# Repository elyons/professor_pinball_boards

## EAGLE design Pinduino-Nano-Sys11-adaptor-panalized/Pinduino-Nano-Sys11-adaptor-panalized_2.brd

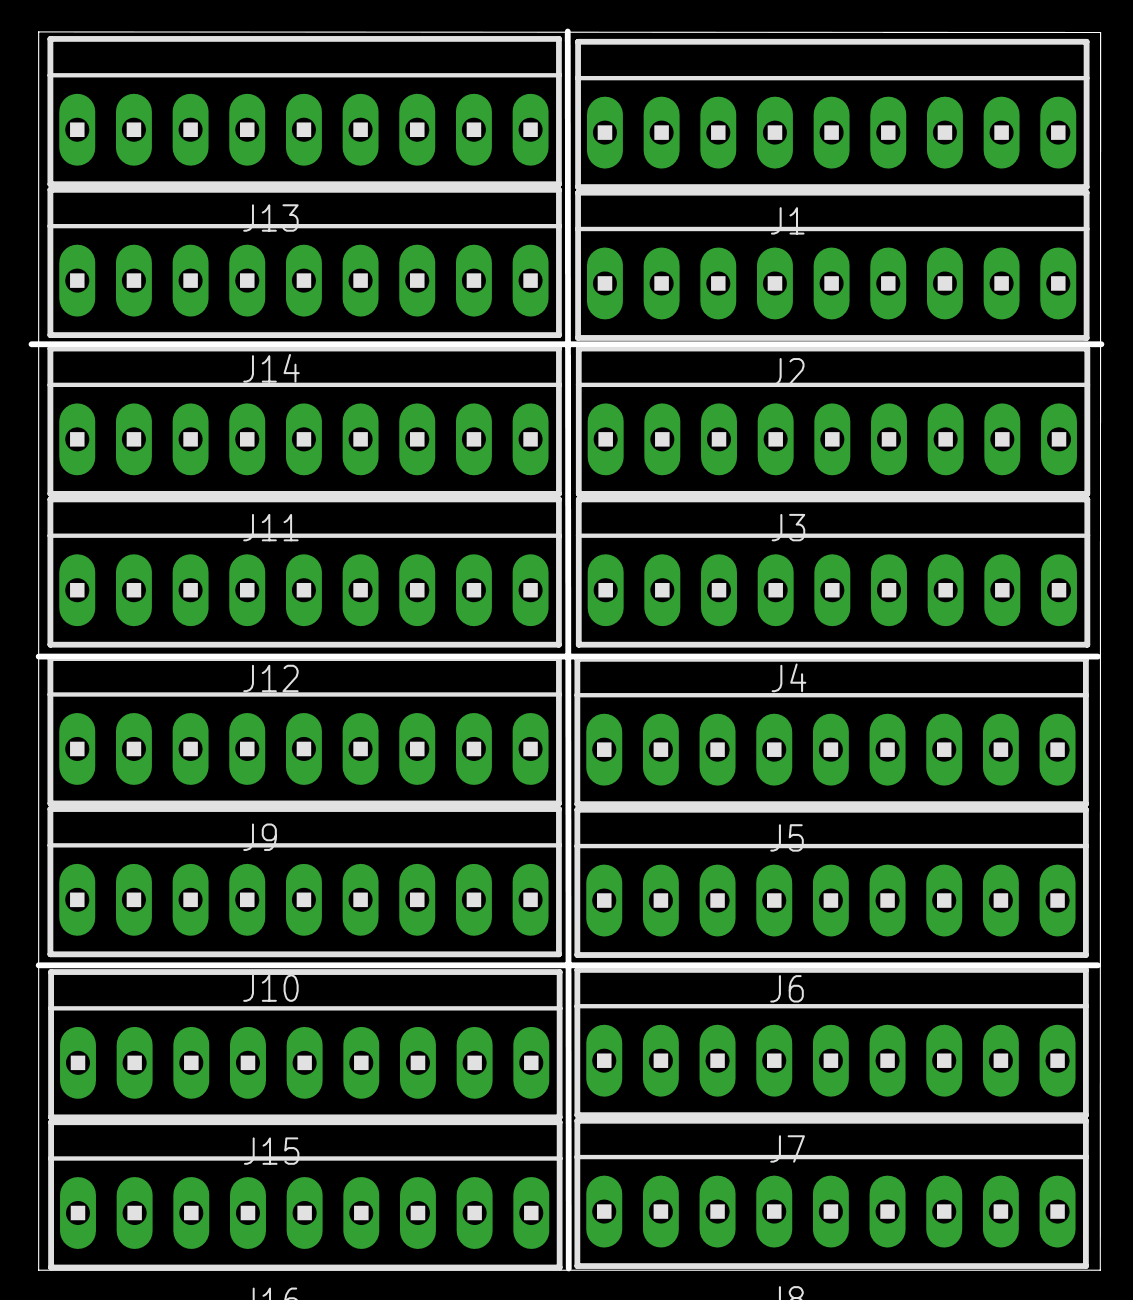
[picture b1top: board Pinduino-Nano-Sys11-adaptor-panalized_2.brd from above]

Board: 2 copper layers, 74.3 x 86.6 mm, 16 parts (0 on the bottom side), 72 nets, no tracks yet.

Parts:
J1, J2, J3, J4, J5, J6, J7, J8, J9, J10, J11, J12, J13, J14, J15, J16: 1X9MTA

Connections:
unnamed: J9.1, J10.1
unnamed: J9.2, J10.2
unnamed: J9.3, J10.3
unnamed: J9.4, J10.4
unnamed: J9.5, J10.5
unnamed: J9.7, J10.7
unnamed: J9.8, J10.8
unnamed: J9.9, J10.9
unnamed: J11.1, J12.1
unnamed: J11.2, J12.2
unnamed: J11.3, J12.3
unnamed: J11.4, J12.4
unnamed: J11.5, J12.5
unnamed: J11.7, J12.7
unnamed: J11.8, J12.8
unnamed: J11.9, J12.9
unnamed: J13.1, J14.1
unnamed: J13.2, J14.2
unnamed: J13.3, J14.3
unnamed: J13.4, J14.4
unnamed: J13.5, J14.5
unnamed: J13.7, J14.7
unnamed: J13.8, J14.8
unnamed: J13.9, J14.9
unnamed: J15.1, J16.1
unnamed: J15.2, J16.2
unnamed: J15.3, J16.3
unnamed: J15.4, J16.4
unnamed: J15.5, J16.5
unnamed: J15.7, J16.7
unnamed: J15.8, J16.8
unnamed: J15.9, J16.9
unnamed: J1.6, J2.6
unnamed: J1.1, J2.1
unnamed: J1.2, J2.2
unnamed: J1.3, J2.3
unnamed: J1.4, J2.4
unnamed: J1.5, J2.5
unnamed: J9.6, J10.6
unnamed: J1.7, J2.7
unnamed: J1.8, J2.8
unnamed: J1.9, J2.9
unnamed: J3.1, J4.1
unnamed: J3.2, J4.2
unnamed: J3.3, J4.3
unnamed: J3.4, J4.4
unnamed: J11.6, J12.6
unnamed: J13.6, J14.6
unnamed: J15.6, J16.6
unnamed: J3.5, J4.5
unnamed: J3.6, J4.6
unnamed: J3.7, J4.7
unnamed: J3.8, J4.8
unnamed: J3.9, J4.9
unnamed: J5.1, J6.1
unnamed: J5.2, J6.2
unnamed: J5.3, J6.3
unnamed: J5.4, J6.4
unnamed: J5.5, J6.5
unnamed: J5.6, J6.6
unnamed: J5.7, J6.7
unnamed: J5.8, J6.8
unnamed: J5.9, J6.9
unnamed: J7.1, J8.1
unnamed: J7.2, J8.2
unnamed: J7.3, J8.3
unnamed: J7.4, J8.4
unnamed: J7.5, J8.5
unnamed: J7.6, J8.6
unnamed: J7.7, J8.7
unnamed: J7.8, J8.8
unnamed: J7.9, J8.9

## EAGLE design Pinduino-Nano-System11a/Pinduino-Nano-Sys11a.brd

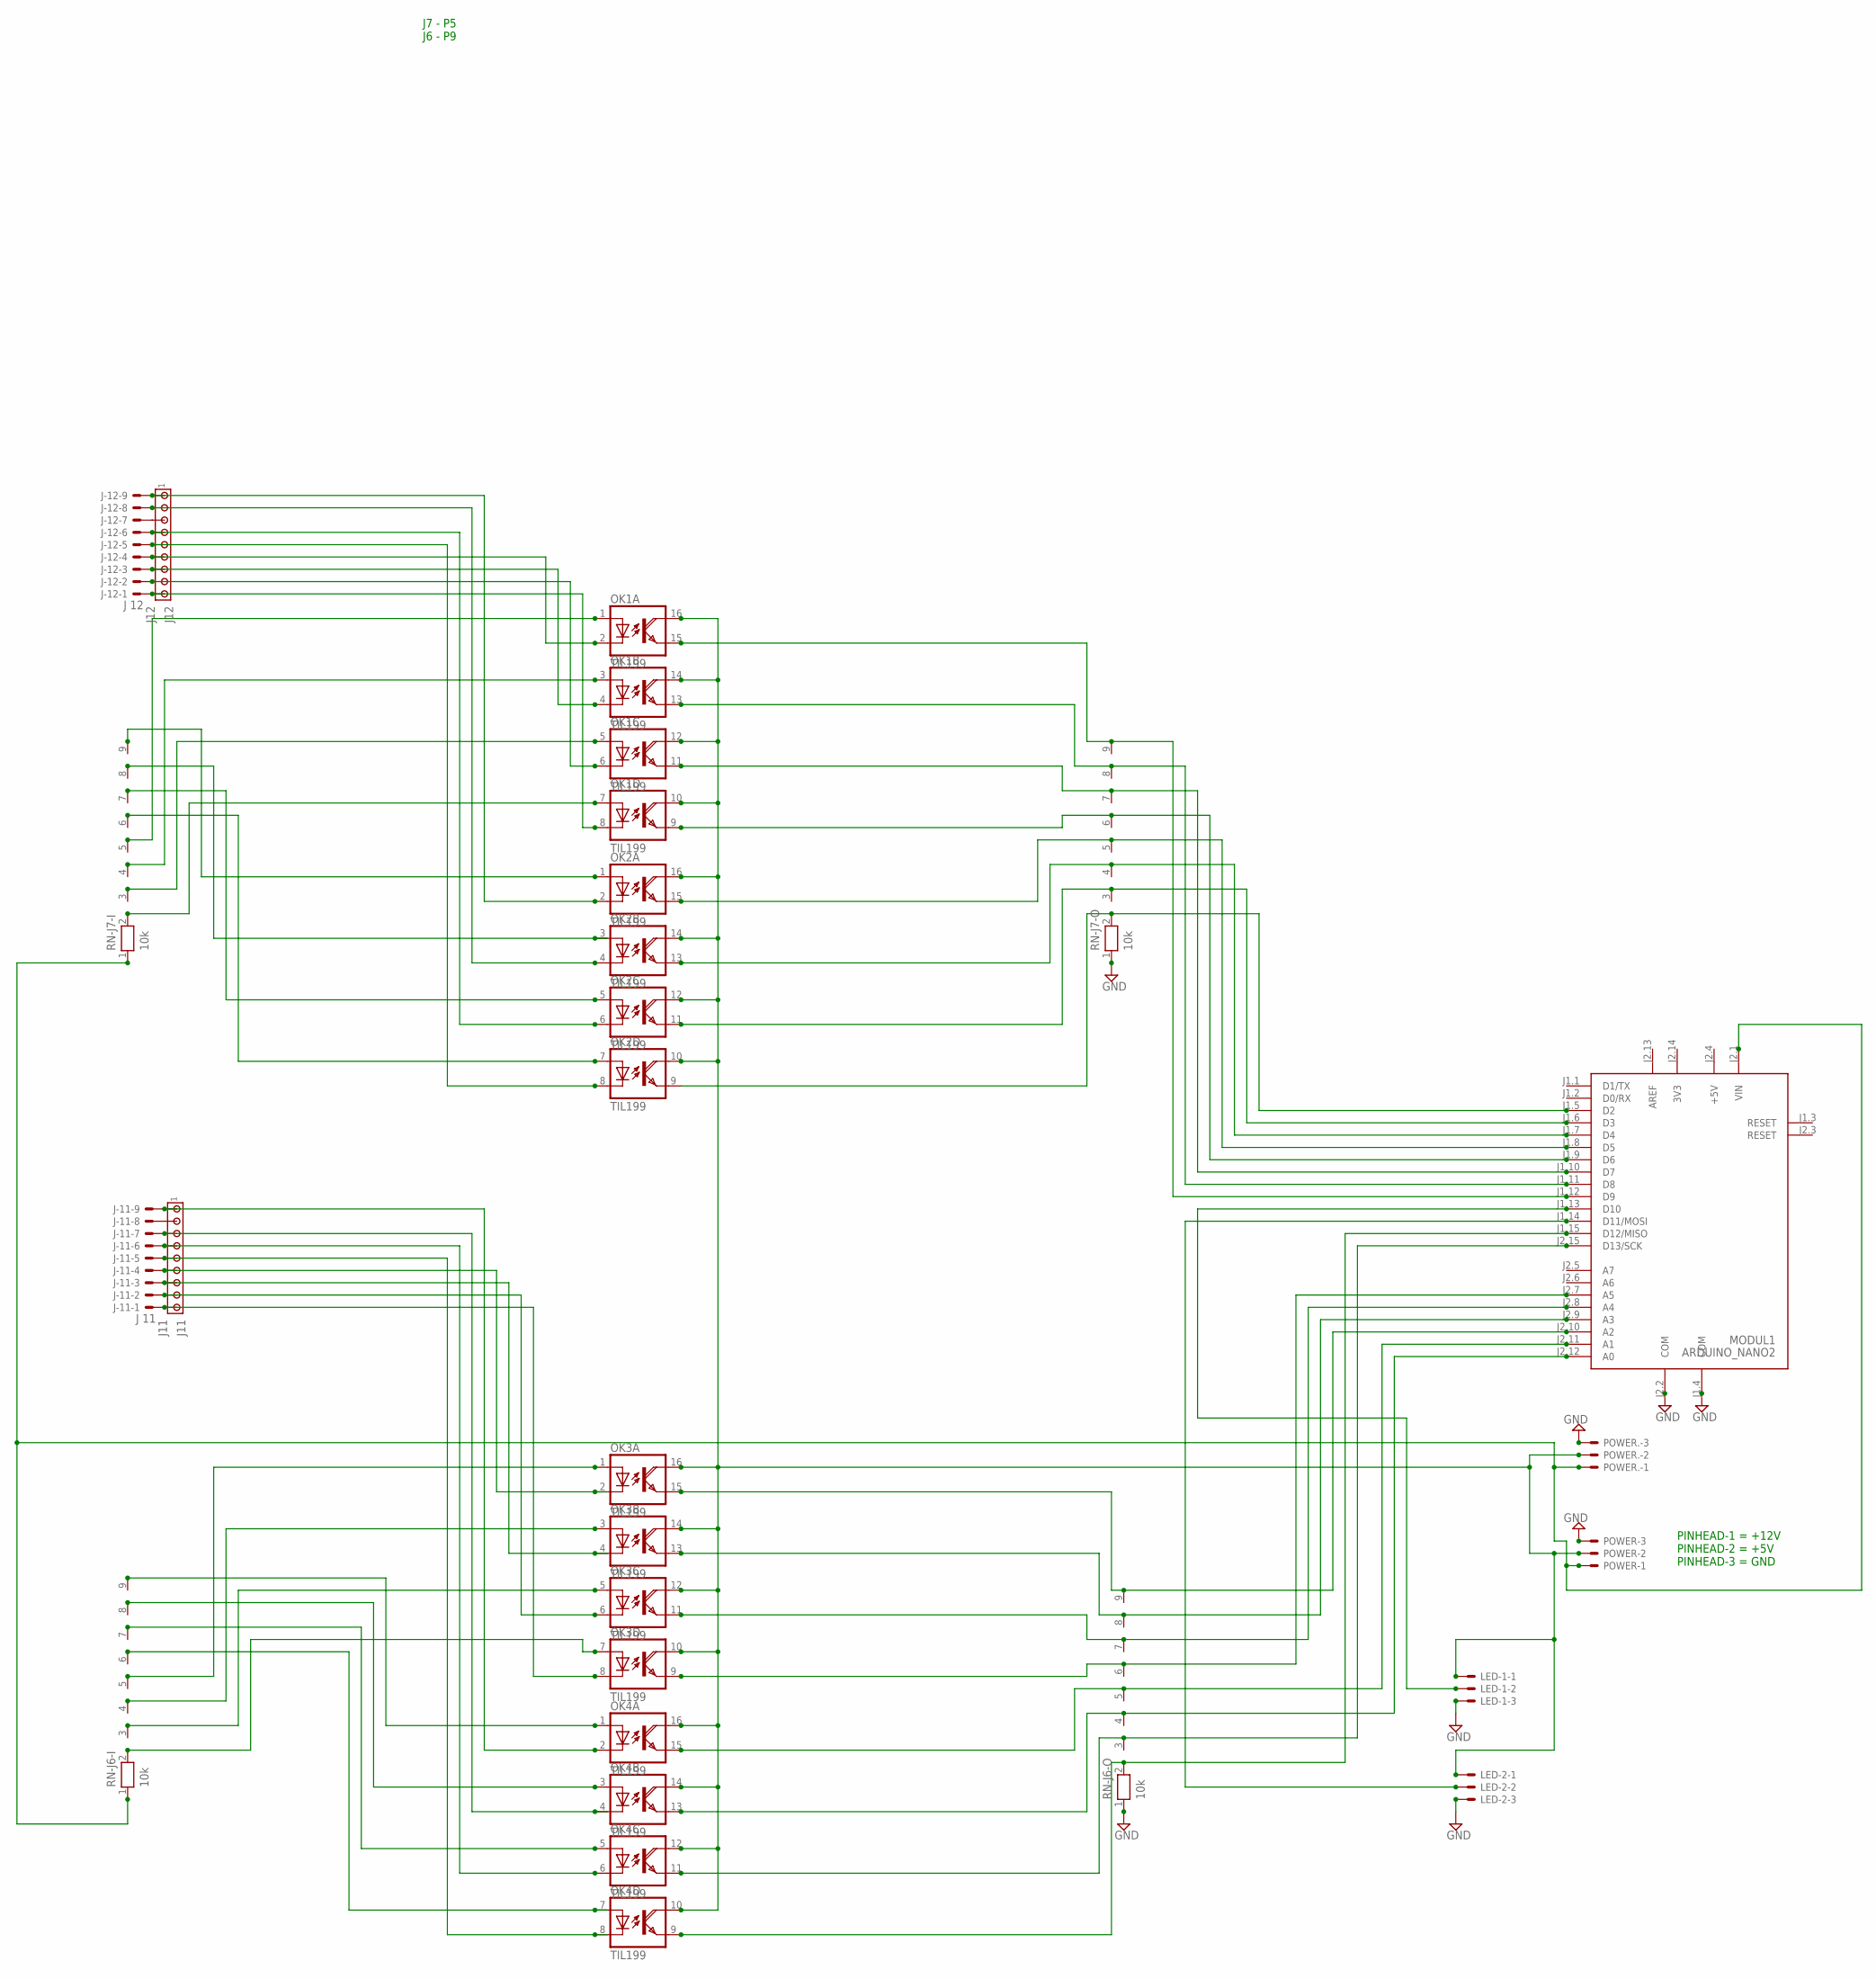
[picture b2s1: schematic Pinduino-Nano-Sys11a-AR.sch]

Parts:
J11: J11; 1X9MTA
J12: J12; 1X9MTA
J-11: J 11; KK-156-9
J-12: J 12; KK-156-9
LED-1, LED-2: 22-23-2031
MODUL1: ARDUINO_NANO2
OK1, OK2, OK3, OK4: TIL199; DIL16
POWER, POWER.: 22-23-2031
RN-J6-I, RN-J6-O, RN-J7-I, RN-J7-O: 10k; RN-9

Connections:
3V3: MODUL1.J2.14 (3V3)
+5V: MODUL1.J2.4 (+5V)
ARD+5V: LED-1.1, LED-2.1, OK1.10 (COL), OK1.12 (COL), OK1.14 (COL), OK1.16 (COL), OK2.10 (COL), OK2.12 (COL), OK2.14 (COL), OK2.16 (COL), OK3.10 (COL), OK3.12 (COL), OK3.14 (COL), OK3.16 (COL), OK4.10 (COL), OK4.12 (COL), OK4.14 (COL), OK4.16 (COL), POWER.2, POWER..2
AREF: MODUL1.J2.13 (AREF)
GND: LED-1.3, LED-2.3, MODUL1.J1.4 (COM), MODUL1.J2.2 (COM), POWER.3, POWER..3, RN-J6-O.1, RN-J7-O.1
unnamed: J12.6, J-12.4, OK1.2 (C)
unnamed: MODUL1.J1.5 (D2), OK2.9 (EMI), RN-J7-O.2
unnamed: OK1.3 (A), RN-J7-I.4
unnamed: OK1.5 (A), RN-J7-I.3
unnamed: OK1.7 (A), RN-J7-I.2
unnamed: OK2.1 (A), RN-J7-I.9
unnamed: OK2.3 (A), RN-J7-I.8
unnamed: OK2.5 (A), RN-J7-I.7
unnamed: OK1.1 (A), RN-J7-I.5
unnamed: J12.9, J-12.1, OK1.8 (C)
unnamed: J12.8, J-12.2, OK1.6 (C)
unnamed: J12.7, J-12.3, OK1.4 (C)
unnamed: OK2.7 (A), RN-J7-I.6
unnamed: J12.5, J-12.5, OK2.8 (C)
unnamed: J11.9, J-11.1, OK3.8 (C)
unnamed: J12.2, J-12.8, OK2.4 (C)
unnamed: J12.1, J-12.9, OK2.2 (C)
unnamed: MODUL1.J1.6 (D3), OK2.11 (EMI), RN-J7-O.3
unnamed: J11.7, J-11.3, OK3.4 (C)
unnamed: J11.5, J-11.5, OK4.8 (C)
unnamed: J11.4, J-11.6, OK4.6 (C)
unnamed: J11.3, J-11.7, OK4.4 (C)
unnamed: J12.3, J-12.7
unnamed: MODUL1.J1.11 (D8), OK1.13 (EMI), RN-J7-O.8
unnamed: J11.2, J-11.8
unnamed: J11.1, J-11.9, OK4.2 (C)
unnamed: MODUL1.J1.7 (D4), OK2.13 (EMI), RN-J7-O.4
unnamed: OK4.1 (A), RN-J6-I.9
unnamed: OK4.3 (A), RN-J6-I.8
unnamed: OK4.5 (A), RN-J6-I.7
unnamed: OK3.3 (A), RN-J6-I.4
unnamed: OK3.1 (A), RN-J6-I.5
unnamed: OK3.5 (A), RN-J6-I.3
unnamed: OK4.7 (A), RN-J6-I.6
unnamed: MODUL1.J2.8 (A4), OK3.11 (EMI), RN-J6-O.7
unnamed: OK3.7 (A), RN-J6-I.2
unnamed: MODUL1.J2.7 (A5), OK3.9 (EMI), RN-J6-O.6
unnamed: MODUL1.J2.15 (D13/SCK), OK4.11 (EMI), RN-J6-O.3
unnamed: J11.8, J-11.2, OK3.6 (C)
unnamed: MODUL1.J2.12 (A0), OK4.13 (EMI), RN-J6-O.4
unnamed: MODUL1.J2.11 (A1), OK4.15 (EMI), RN-J6-O.5
unnamed: LED-2.2, MODUL1.J1.14 (D11/MOSI)
unnamed: LED-1.2, MODUL1.J1.13 (D10)
unnamed: MODUL1.J1.12 (D9), OK1.15 (EMI), RN-J7-O.9
unnamed: J12.4, J-12.6, OK2.6 (C)
unnamed: J11.6, J-11.4, OK3.2 (C)
unnamed: MODUL1.J1.10 (D7), OK1.11 (EMI), RN-J7-O.7
unnamed: MODUL1.J1.8 (D5), OK2.15 (EMI), RN-J7-O.5
unnamed: MODUL1.J1.9 (D6), OK1.9 (EMI), RN-J7-O.6
unnamed: MODUL1.J2.9 (A3), OK3.13 (EMI), RN-J6-O.8
unnamed: MODUL1.J2.10 (A2), OK3.15 (EMI), RN-J6-O.9
unnamed: MODUL1.J1.15 (D12/MISO), OK4.9 (EMI), RN-J6-O.2
unnamed: MODUL1.J2.1 (VIN), POWER.1, POWER..1, RN-J6-I.1, RN-J7-I.1

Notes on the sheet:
J7 - P5 J6 - P9
PINHEAD-1 = +12V PINHEAD-2 = +5V PINHEAD-3 = GND

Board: 2 copper layers, 17 parts (0 on the bottom side), 55 nets, no tracks yet.

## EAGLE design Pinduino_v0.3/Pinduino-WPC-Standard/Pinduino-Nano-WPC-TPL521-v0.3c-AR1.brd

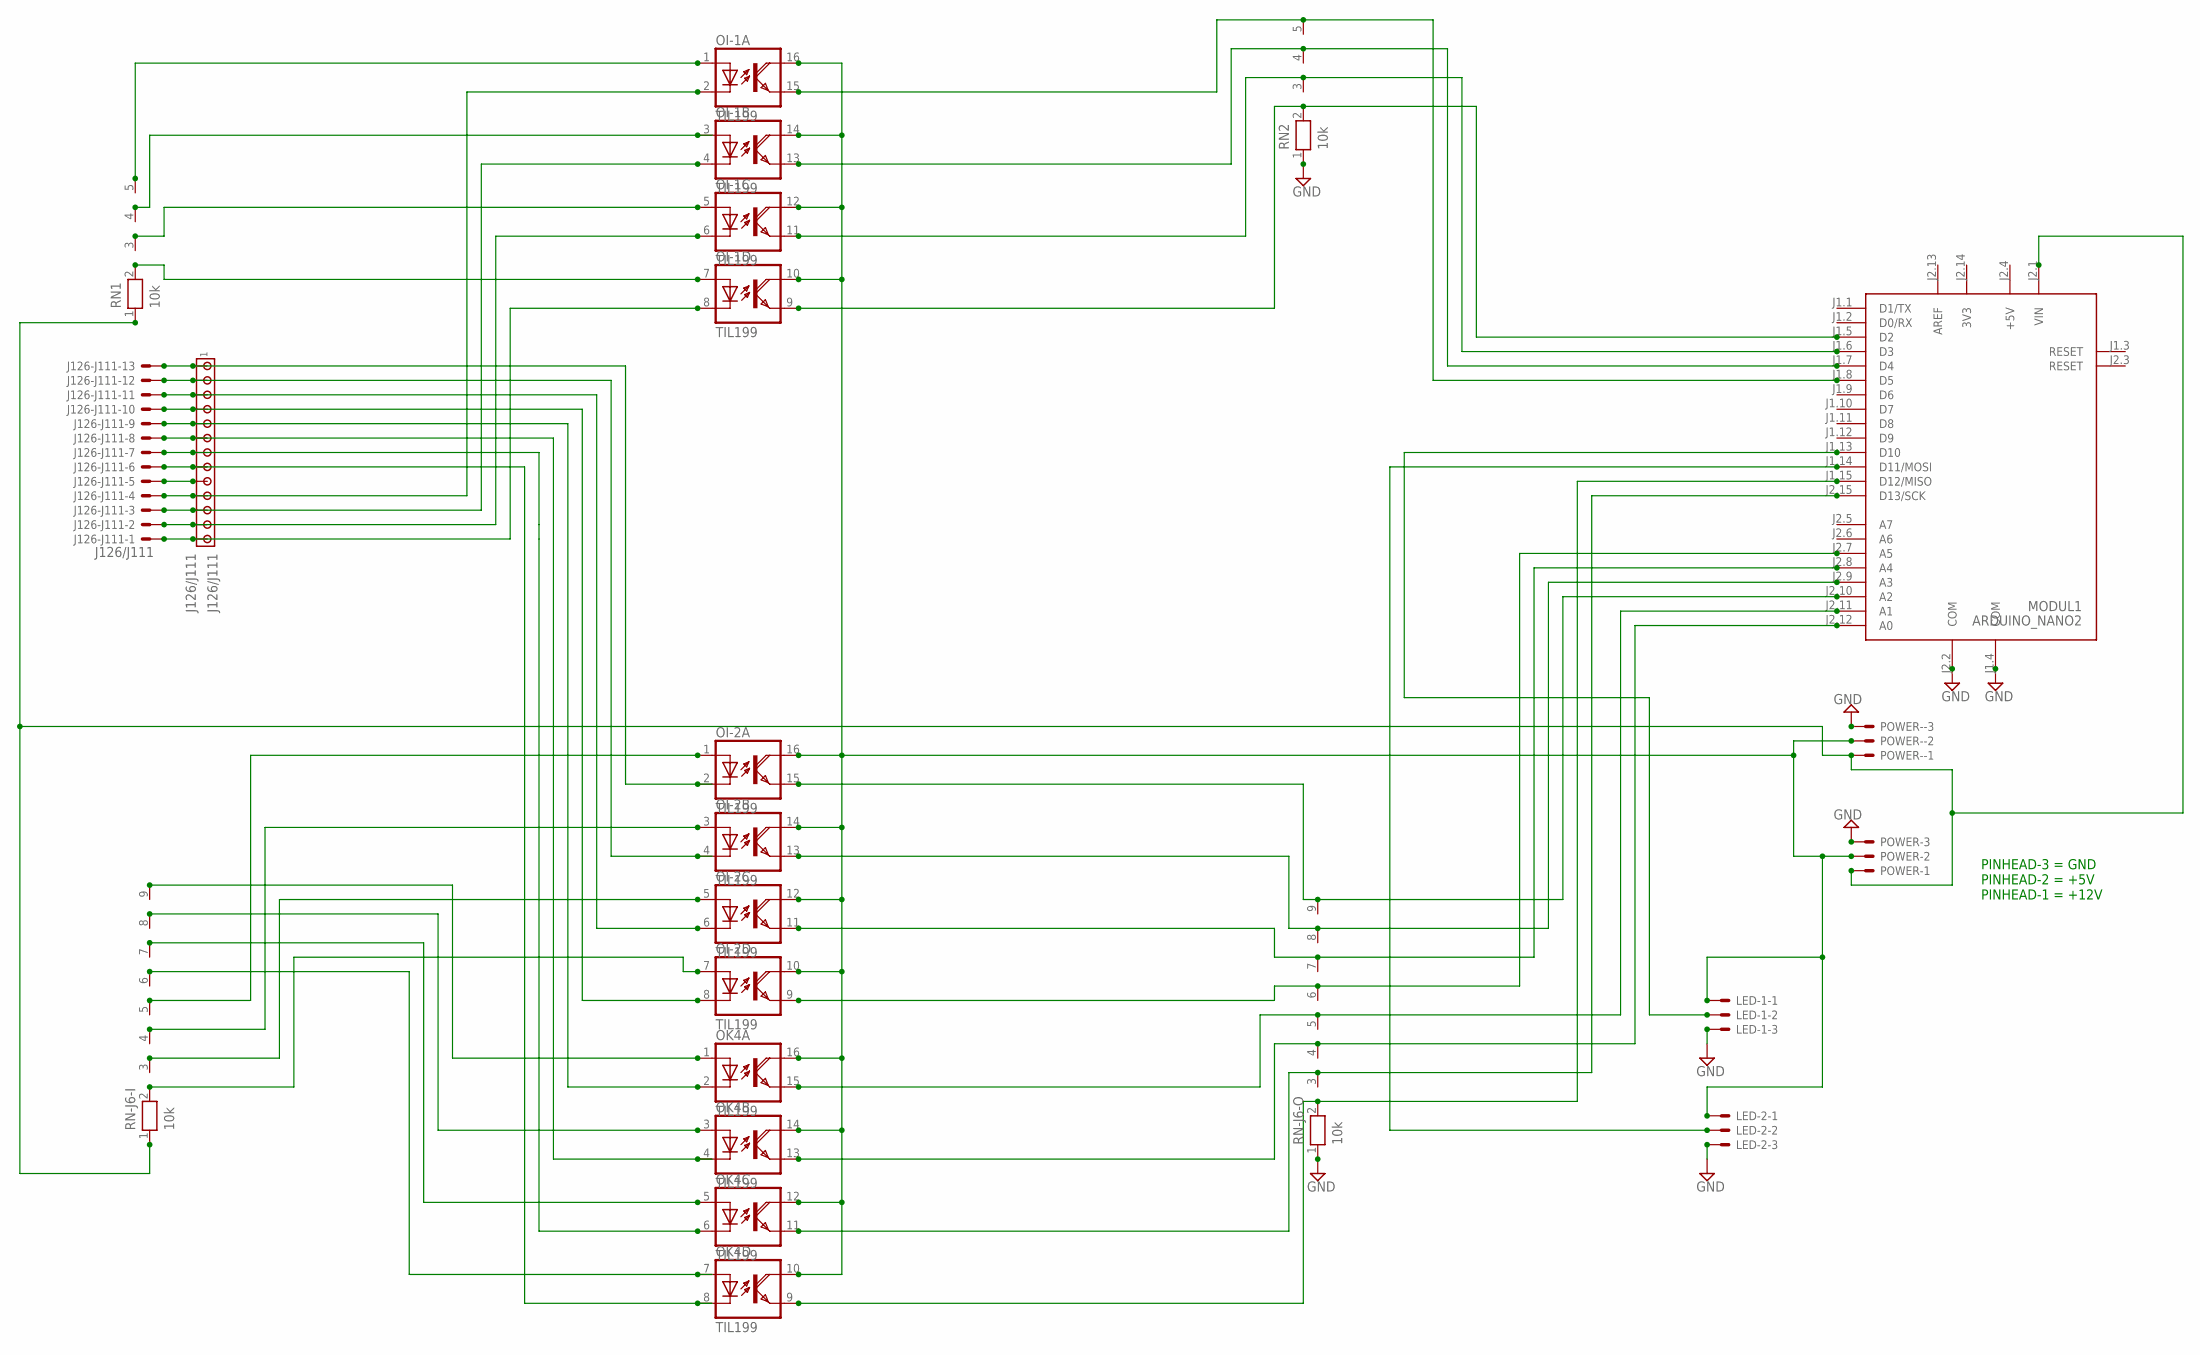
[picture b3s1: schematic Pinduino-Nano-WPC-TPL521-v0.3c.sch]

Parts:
J126-J111: J126/J111; KK-156-13
J126/J111: J126/J111; 1X13MTA
LED-1, LED-2: 22-23-2031
MODUL1: ARDUINO_NANO2
OI-1, OI-2: TIL199; DIL16
OK4: TIL199; DIL16
POWER: 22-23-2031
POWER-: 22-23-2031
RN1, RN2: 10k; RN-5
RN-J6-I, RN-J6-O: 10k; RN-9

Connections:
3V3: MODUL1.J2.14 (3V3)
+5V: MODUL1.J2.4 (+5V)
ARD+5V: LED-1.1, LED-2.1, OI-1.10 (COL), OI-1.12 (COL), OI-1.14 (COL), OI-1.16 (COL), OI-2.10 (COL), OI-2.12 (COL), OI-2.14 (COL), OI-2.16 (COL), OK4.10 (COL), OK4.12 (COL), OK4.14 (COL), OK4.16 (COL), POWER.2, POWER-.2
AREF: MODUL1.J2.13 (AREF)
GND: LED-1.3, LED-2.3, MODUL1.J1.4 (COM), MODUL1.J2.2 (COM), POWER.3, POWER-.3, RN2.1, RN-J6-O.1
unnamed: MODUL1.J2.1 (VIN), POWER.1, POWER-.1, RN1.1, RN-J6-I.1
unnamed: MODUL1.J1.5 (D2), OI-1.9 (EMI), RN2.2
unnamed: OI-1.5 (A), RN1.3
unnamed: OI-1.1 (A), RN1.5
unnamed: OI-1.3 (A), RN1.4
unnamed: OI-1.7 (A), RN1.2
unnamed: MODUL1.J1.6 (D3), OI-1.11 (EMI), RN2.3
unnamed: J126-J111.3, J126/J111.11, OI-1.4 (C)
unnamed: J126-J111.2, J126/J111.12, OI-1.6 (C)
unnamed: J126-J111.12, J126/J111.2, OI-2.4 (C)
unnamed: J126-J111.13, J126/J111.1, OI-2.2 (C)
unnamed: J126-J111.4, J126/J111.10, OI-1.2 (C)
unnamed: J126-J111.1, J126/J111.13, OI-1.8 (C)
unnamed: J126-J111.9, J126/J111.5, OK4.2 (C)
unnamed: MODUL1.J1.7 (D4), OI-1.13 (EMI), RN2.4
unnamed: OK4.1 (A), RN-J6-I.9
unnamed: OK4.3 (A), RN-J6-I.8
unnamed: OK4.5 (A), RN-J6-I.7
unnamed: OI-2.3 (A), RN-J6-I.4
unnamed: OI-2.1 (A), RN-J6-I.5
unnamed: OI-2.5 (A), RN-J6-I.3
unnamed: OK4.7 (A), RN-J6-I.6
unnamed: MODUL1.J2.8 (A4), OI-2.11 (EMI), RN-J6-O.7
unnamed: OI-2.7 (A), RN-J6-I.2
unnamed: MODUL1.J2.7 (A5), OI-2.9 (EMI), RN-J6-O.6
unnamed: MODUL1.J2.15 (D13/SCK), OK4.11 (EMI), RN-J6-O.3
unnamed: MODUL1.J2.12 (A0), OK4.13 (EMI), RN-J6-O.4
unnamed: MODUL1.J2.11 (A1), OK4.15 (EMI), RN-J6-O.5
unnamed: LED-2.2, MODUL1.J1.14 (D11/MOSI)
unnamed: LED-1.2, MODUL1.J1.13 (D10)
unnamed: MODUL1.J1.8 (D5), OI-1.15 (EMI), RN2.5
unnamed: MODUL1.J2.9 (A3), OI-2.13 (EMI), RN-J6-O.8
unnamed: MODUL1.J2.10 (A2), OI-2.15 (EMI), RN-J6-O.9
unnamed: J126-J111.6, J126/J111.8, OK4.8 (C)
unnamed: J126-J111.7, J126/J111.7, OK4.6 (C)
unnamed: MODUL1.J1.15 (D12/MISO), OK4.9 (EMI), RN-J6-O.2
unnamed: J126-J111.8, J126/J111.6, OK4.4 (C)
unnamed: J126-J111.5, J126/J111.9
unnamed: J126-J111.10, J126/J111.4, OI-2.8 (C)
unnamed: J126-J111.11, J126/J111.3, OI-2.6 (C)

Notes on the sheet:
PINHEAD-3 = GND PINHEAD-2 = +5V PINHEAD-1 = +12V

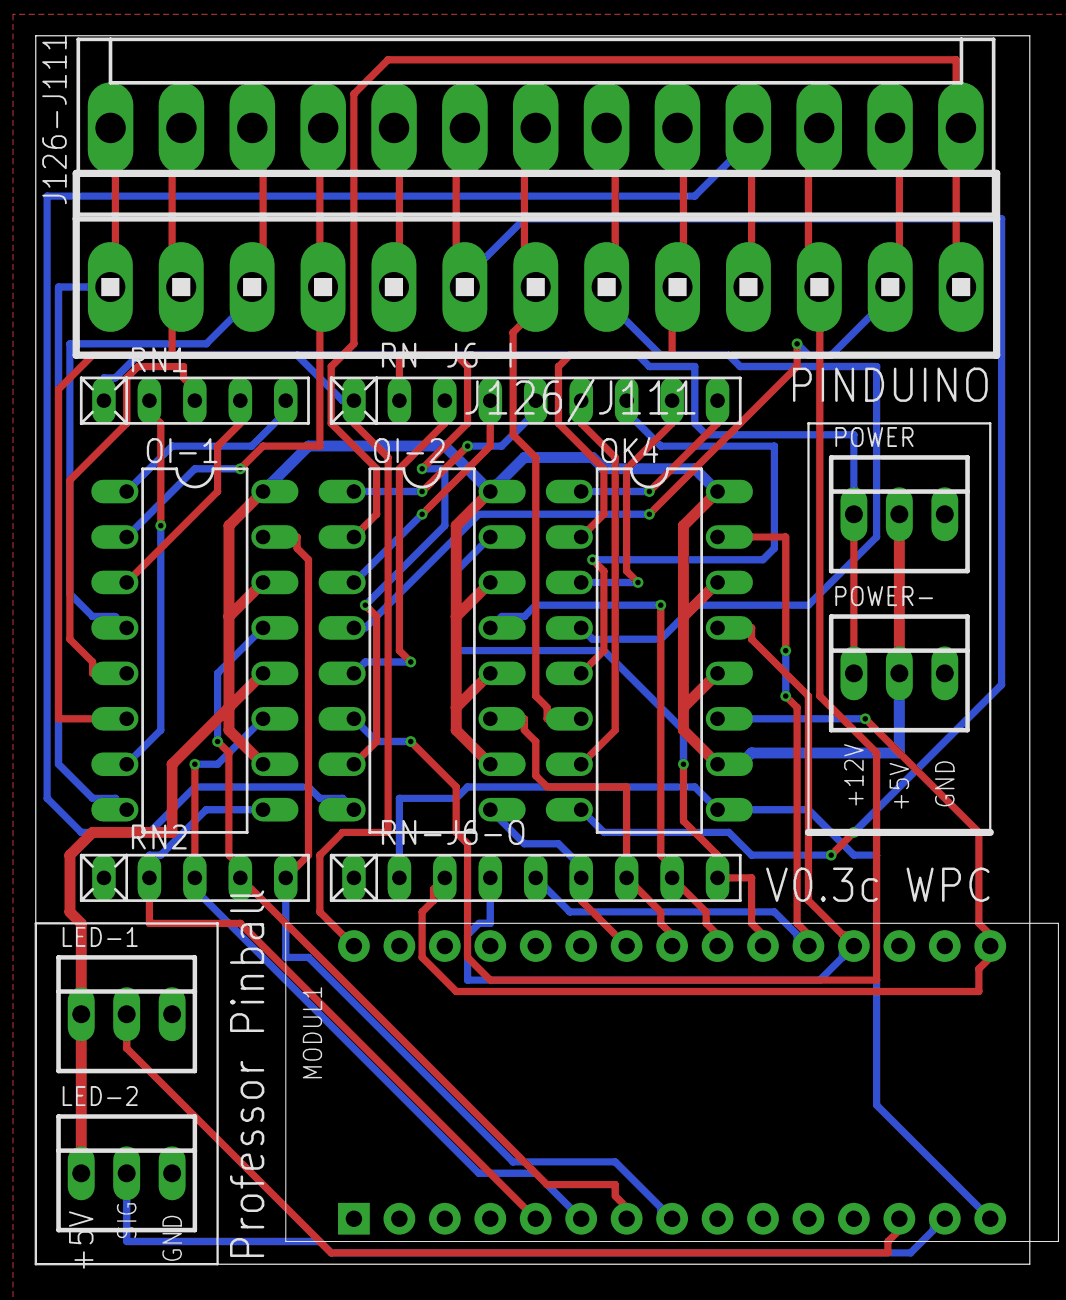
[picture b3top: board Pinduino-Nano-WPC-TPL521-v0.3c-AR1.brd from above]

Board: 2 copper layers, 55.6 x 68.7 mm, 14 parts (0 on the bottom side), 42 nets.

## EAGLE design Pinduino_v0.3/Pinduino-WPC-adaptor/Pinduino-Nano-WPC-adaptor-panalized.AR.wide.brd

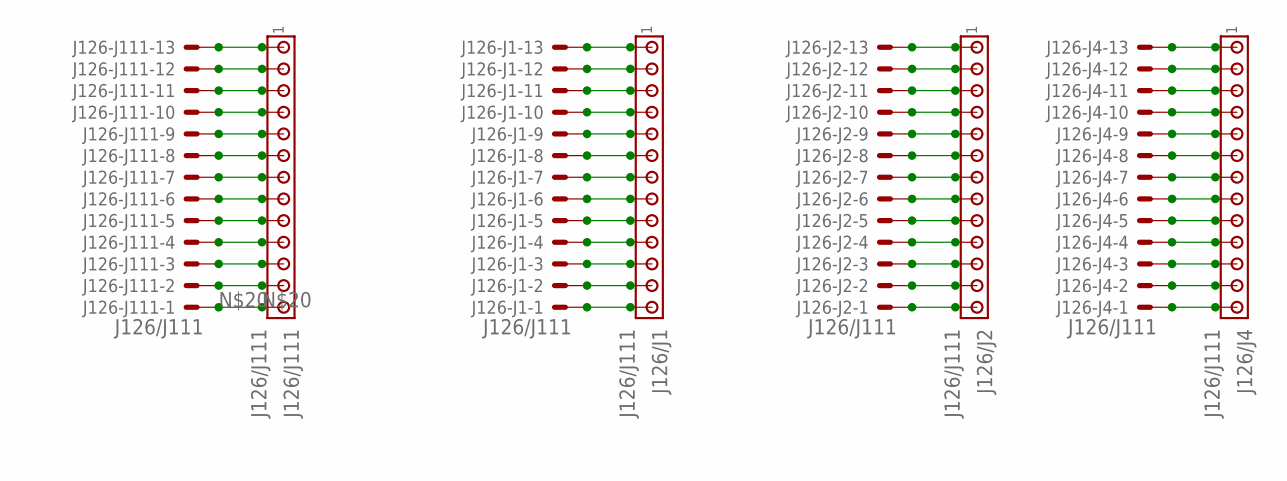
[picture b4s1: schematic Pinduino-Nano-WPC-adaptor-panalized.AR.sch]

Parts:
J126-J1, J126-J2, J126-J4, J126-J111: J126/J111; KK-156-13
J126/J1, J126/J2, J126/J4, J126/J111: J126/J111; 1X13MTA

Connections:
unnamed: J126-J1.12, J126/J1.2
unnamed: J126-J1.13, J126/J1.1
unnamed: J126-J1.9, J126/J1.5
unnamed: J126-J1.5, J126/J1.9
unnamed: J126-J1.6, J126/J1.8
unnamed: J126-J1.7, J126/J1.7
unnamed: J126-J1.8, J126/J1.6
unnamed: J126-J1.10, J126/J1.4
unnamed: J126-J1.11, J126/J1.3
unnamed: J126-J1.4, J126/J1.10
unnamed: J126-J1.3, J126/J1.11
unnamed: J126-J1.2, J126/J1.12
unnamed: J126-J1.1, J126/J1.13
unnamed: J126-J2.12, J126/J2.2
unnamed: J126-J2.13, J126/J2.1
unnamed: J126-J2.9, J126/J2.5
unnamed: J126-J2.5, J126/J2.9
unnamed: J126-J2.6, J126/J2.8
unnamed: J126-J111.3, J126/J111.11
unnamed: J126-J111.2, J126/J111.12
unnamed: J126-J111.12, J126/J111.2
unnamed: J126-J111.13, J126/J111.1
unnamed: J126-J111.4, J126/J111.10
unnamed: J126-J2.7, J126/J2.7
unnamed: J126-J111.1, J126/J111.13
unnamed: J126-J2.8, J126/J2.6
unnamed: J126-J111.9, J126/J111.5
unnamed: J126-J2.10, J126/J2.4
unnamed: J126-J2.11, J126/J2.3
unnamed: J126-J2.4, J126/J2.10
unnamed: J126-J2.3, J126/J2.11
unnamed: J126-J2.2, J126/J2.12
unnamed: J126-J2.1, J126/J2.13
unnamed: J126-J4.12, J126/J4.2
unnamed: J126-J4.13, J126/J4.1
unnamed: J126-J4.9, J126/J4.5
unnamed: J126-J4.5, J126/J4.9
unnamed: J126-J4.6, J126/J4.8
unnamed: J126-J4.7, J126/J4.7
unnamed: J126-J4.8, J126/J4.6
unnamed: J126-J4.10, J126/J4.4
unnamed: J126-J4.11, J126/J4.3
unnamed: J126-J4.4, J126/J4.10
unnamed: J126-J4.3, J126/J4.11
unnamed: J126-J111.6, J126/J111.8
unnamed: J126-J111.7, J126/J111.7
unnamed: J126-J4.2, J126/J4.12
unnamed: J126-J4.1, J126/J4.13
unnamed: J126-J111.8, J126/J111.6
unnamed: J126-J111.5, J126/J111.9
unnamed: J126-J111.10, J126/J111.4
unnamed: J126-J111.11, J126/J111.3

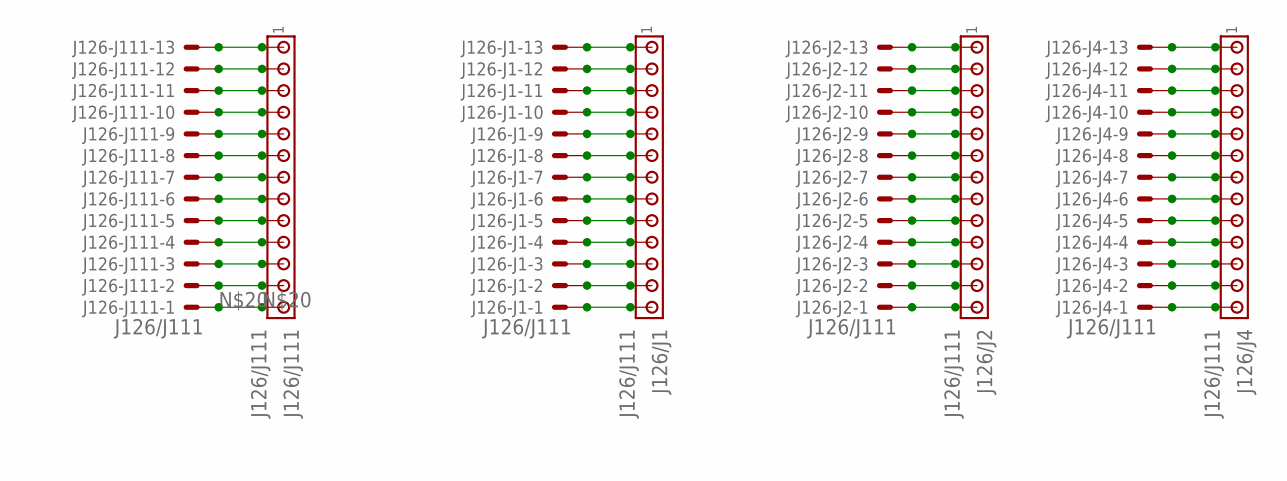
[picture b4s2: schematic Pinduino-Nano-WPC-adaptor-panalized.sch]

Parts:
J126-J1, J126-J2, J126-J4, J126-J111: J126/J111; KK-156-13
J126/J1, J126/J2, J126/J4, J126/J111: J126/J111; 1X13MTA

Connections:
unnamed: J126-J1.12, J126/J1.2
unnamed: J126-J1.13, J126/J1.1
unnamed: J126-J1.9, J126/J1.5
unnamed: J126-J1.5, J126/J1.9
unnamed: J126-J1.6, J126/J1.8
unnamed: J126-J1.7, J126/J1.7
unnamed: J126-J1.8, J126/J1.6
unnamed: J126-J1.10, J126/J1.4
unnamed: J126-J1.11, J126/J1.3
unnamed: J126-J1.4, J126/J1.10
unnamed: J126-J1.3, J126/J1.11
unnamed: J126-J1.2, J126/J1.12
unnamed: J126-J1.1, J126/J1.13
unnamed: J126-J2.12, J126/J2.2
unnamed: J126-J2.13, J126/J2.1
unnamed: J126-J2.9, J126/J2.5
unnamed: J126-J2.5, J126/J2.9
unnamed: J126-J2.6, J126/J2.8
unnamed: J126-J111.3, J126/J111.11
unnamed: J126-J111.2, J126/J111.12
unnamed: J126-J111.12, J126/J111.2
unnamed: J126-J111.13, J126/J111.1
unnamed: J126-J111.4, J126/J111.10
unnamed: J126-J2.7, J126/J2.7
unnamed: J126-J111.1, J126/J111.13
unnamed: J126-J2.8, J126/J2.6
unnamed: J126-J111.9, J126/J111.5
unnamed: J126-J2.10, J126/J2.4
unnamed: J126-J2.11, J126/J2.3
unnamed: J126-J2.4, J126/J2.10
unnamed: J126-J2.3, J126/J2.11
unnamed: J126-J2.2, J126/J2.12
unnamed: J126-J2.1, J126/J2.13
unnamed: J126-J4.12, J126/J4.2
unnamed: J126-J4.13, J126/J4.1
unnamed: J126-J4.9, J126/J4.5
unnamed: J126-J4.5, J126/J4.9
unnamed: J126-J4.6, J126/J4.8
unnamed: J126-J4.7, J126/J4.7
unnamed: J126-J4.8, J126/J4.6
unnamed: J126-J4.10, J126/J4.4
unnamed: J126-J4.11, J126/J4.3
unnamed: J126-J4.4, J126/J4.10
unnamed: J126-J4.3, J126/J4.11
unnamed: J126-J111.6, J126/J111.8
unnamed: J126-J111.7, J126/J111.7
unnamed: J126-J4.2, J126/J4.12
unnamed: J126-J4.1, J126/J4.13
unnamed: J126-J111.8, J126/J111.6
unnamed: J126-J111.5, J126/J111.9
unnamed: J126-J111.10, J126/J111.4
unnamed: J126-J111.11, J126/J111.3

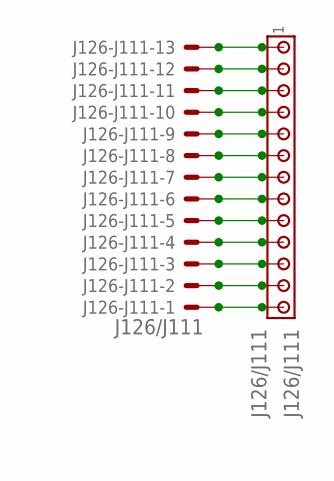
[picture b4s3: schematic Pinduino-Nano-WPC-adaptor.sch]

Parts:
J126-J111: J126/J111; KK-156-13
J126/J111: J126/J111; 1X13MTA

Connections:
unnamed: J126-J111.3, J126/J111.11
unnamed: J126-J111.2, J126/J111.12
unnamed: J126-J111.12, J126/J111.2
unnamed: J126-J111.13, J126/J111.1
unnamed: J126-J111.4, J126/J111.10
unnamed: J126-J111.1, J126/J111.13
unnamed: J126-J111.9, J126/J111.5
unnamed: J126-J111.6, J126/J111.8
unnamed: J126-J111.7, J126/J111.7
unnamed: J126-J111.8, J126/J111.6
unnamed: J126-J111.5, J126/J111.9
unnamed: J126-J111.10, J126/J111.4
unnamed: J126-J111.11, J126/J111.3

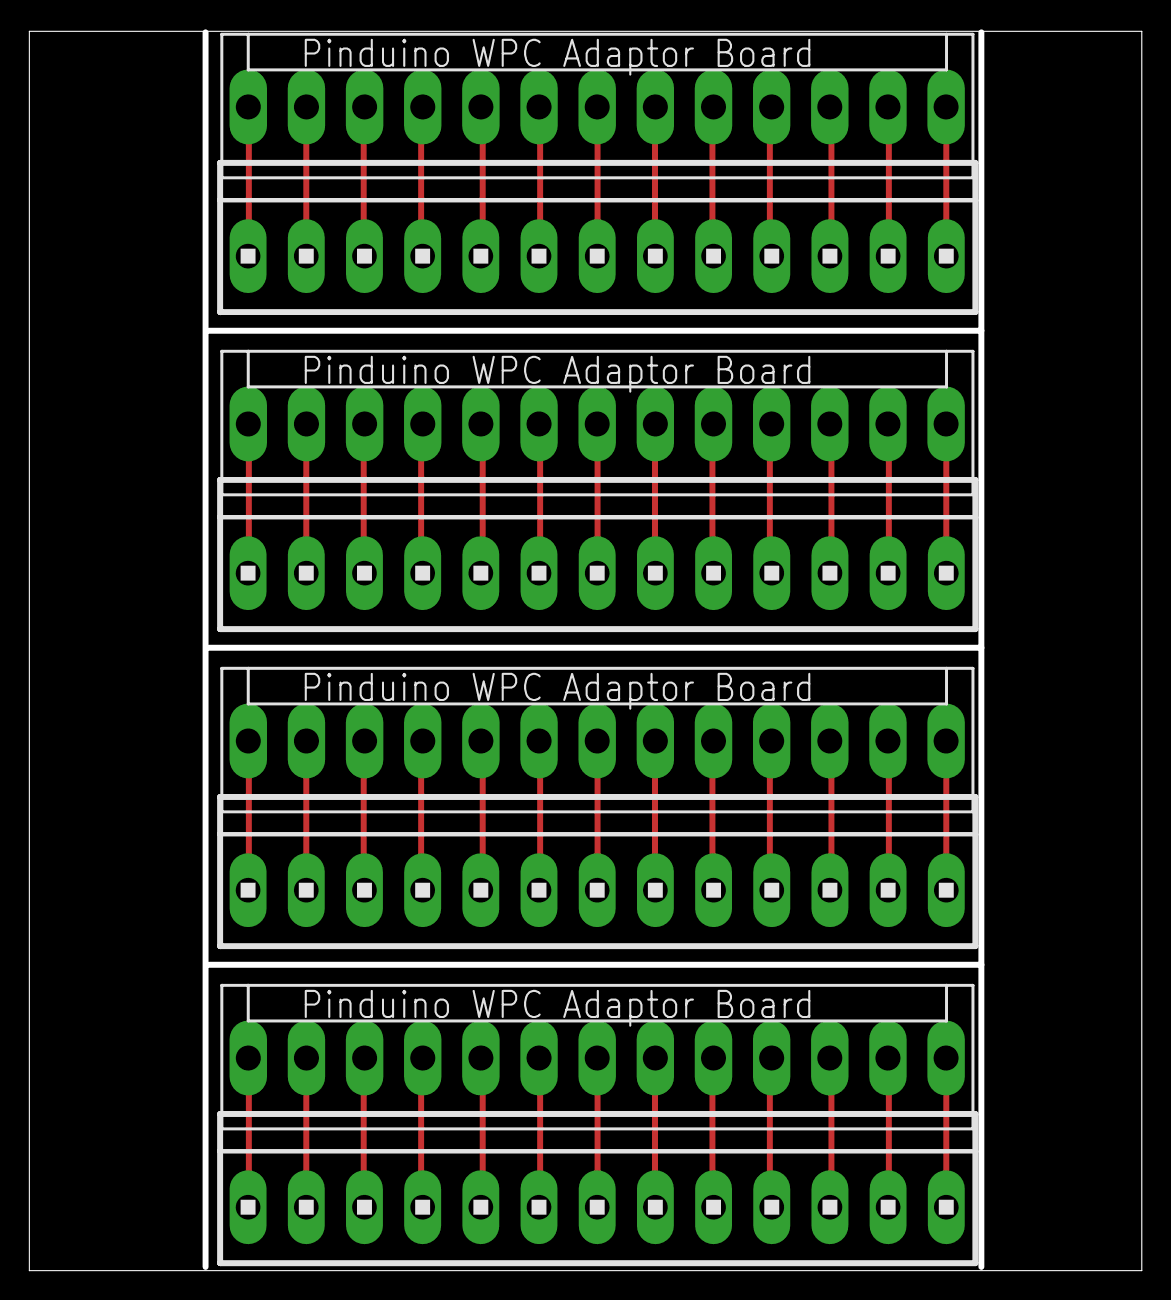
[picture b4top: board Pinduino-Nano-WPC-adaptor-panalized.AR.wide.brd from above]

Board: 2 copper layers, 75.8 x 84.4 mm, 8 parts (0 on the bottom side), 52 nets.

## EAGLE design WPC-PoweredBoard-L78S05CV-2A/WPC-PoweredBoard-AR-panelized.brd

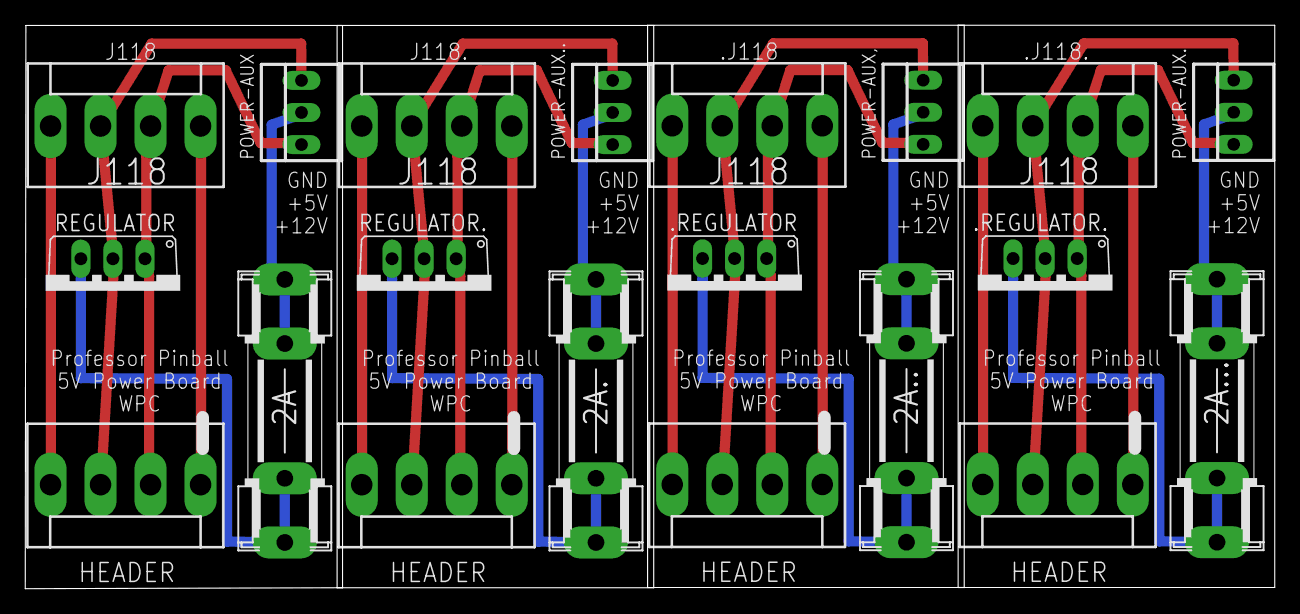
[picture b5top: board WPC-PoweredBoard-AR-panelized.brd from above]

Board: 2 copper layers, 98.9 x 44.6 mm, 20 parts (0 on the bottom side), 24 nets.

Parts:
2A, 2A., 2A.., 2A...: FUSESHK20L; SHK20L
.J118, .J118.: Plug; KK-156-4
.REGULATOR, .REGULATOR.: 786TV; TO220V
J118, J118.: Plug; KK-156-4
PDB, PDB1, PDB2, PDB3: PDB; KK-156-4
POWER-AUX, POWER-AUX., POWER-AUX..: 22-23-2031
POWER-AUX,: 22-23-2031
REGULATOR, REGULATOR.: 786TV; TO220V

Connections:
unnamed: J118.1, PDB.4
unnamed: J118.3, PDB.2, POWER-AUX.1, REGULATOR.1
unnamed: J118.2, PDB.3, POWER-AUX.3, REGULATOR.2
unnamed: 2A.2A, POWER-AUX.2
unnamed: 2A.1A, REGULATOR.3
unnamed: J118.4, PDB.1
unnamed: J118..3, PDB1.2, POWER-AUX...1, REGULATOR..1
unnamed: J118..2, PDB1.3, POWER-AUX...3, REGULATOR..2
unnamed: J118..1, PDB1.4
unnamed: 2A..1A, REGULATOR..3
unnamed: 2A..2A, POWER-AUX...2
unnamed: J118..4, PDB1.1
unnamed: .J118.3, .REGULATOR.1, PDB2.2, POWER-AUX,.1
unnamed: .J118.2, .REGULATOR.2, PDB2.3, POWER-AUX,.3
unnamed: .J118.1, PDB2.4
unnamed: 2A...1A, .REGULATOR.3
unnamed: 2A...2A, POWER-AUX,.2
unnamed: .J118.4, PDB2.1
unnamed: .J118..3, .REGULATOR..1, PDB3.2, POWER-AUX..1
unnamed: .J118..2, .REGULATOR..2, PDB3.3, POWER-AUX..3
unnamed: .J118..1, PDB3.4
unnamed: 2A....1A, .REGULATOR..3
unnamed: 2A....2A, POWER-AUX..2
unnamed: .J118..4, PDB3.1
